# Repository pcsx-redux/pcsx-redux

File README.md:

<a href='https://ko-fi.com/nicolasnoble' target='_blank'>Buy Me a Coffee at ko-fi.com</a>

|Platform|Build status|Download|
|--------|------------|--------|
|Windows x64 build||[Windows Intel 64-bits](https://distrib.app/pub/org/pcsx-redux/project/dev-win-x64)|
|Linux x64 build||[Linux Intel 64-bits (AppImage)](https://distrib.app/pub/org/pcsx-redux/project/dev-linux-x64)|
|Linux arm64 build||[Linux Arm 64-bits (AppImage)](https://distrib.app/pub/org/pcsx-redux/project/dev-linux-arm64)|
|macOS build||[macOS Arm](https://distrib.app/pub/org/pcsx-redux/project/dev-macos-arm)|
|Browser build||[Run in the browser (experimental)](https://tools.psx.dev/redux/)|

To discuss this emulator specifically, please join our Discord server:

To discuss PlayStation 1 development, hacking, and reverse engineering in general, please join the PSX.Dev Discord server:

# PCSX-Redux

## What?
The PCSX-Redux project is a collection of tools, research, hardware design, and libraries aiming at development and reverse engineering on the PlayStation 1. The core product itself, PCSX-Redux, is yet another fork of the Playstation emulator, PCSX. While the work here is very much in progress, the goal is roughly the following:

 - Bring the codebase to more up to date code standards.
 - Get rid of the plugin system and create a single monolithic codebase that handles all aspects of the playstation emulation.
 - Write everything on top of OpenGL3+/ImGui for portability and readability.
 - Improve the debugging experience.
 - Improve the rendering experience.

Please consult [the documentation pages](https://pcsx-redux.consoledev.net) for more information on the emulator itself.

The [tools](tools) directory contains a few tools that can be used to work with PlayStation 1 software. The [wiki](https://github.com/pcsx-redux/pcsx-redux/wiki) directory contains a few research information that are not directly related to the emulator itself. The [mips](https://github.com/pcsx-redux/nugget) directory (the nugget submodule, checked out at `src/mips`) contains various pieces of code targeting the PlayStation 1, and importantly, the OpenBIOS project, which is a MIPS R3000A BIOS implementation that can be used to boot PlayStation 1 games without the need for a retail BIOS. And the [hardware](hardware) directory contains various hardware designs that can be used with the PlayStation 1.

## Where?
|Download page|
|--------|
|[Windows Intel 64-bits](https://distrib.app/pub/org/pcsx-redux/project/dev-win-x64)|
|[Windows Intel 64-bits CLI](https://distrib.app/pub/org/pcsx-redux/project/dev-win-cli-x64)|
|[Linux Intel 64-bits (AppImage)](https://distrib.app/pub/org/pcsx-redux/project/dev-linux-x64)|
|[Linux Arm 64-bits (AppImage)](https://distrib.app/pub/org/pcsx-redux/project/dev-linux-arm64)|
|[MacOS Arm](https://distrib.app/pub/org/pcsx-redux/project/dev-macos-arm)|
|[Browser (WebAssembly, experimental)](https://tools.psx.dev/redux/)|

All native builds are 64-bit only, and need a GPU and driver that can create at least an OpenGL 3.0 context. The emulator asks for a 3.3 core profile first and falls back to 3.0 if that fails.

The browser build is highly experimental and not really functional yet: expect missing features and breakage. It is redeployed from each push to main whose wasm build succeeds. It runs the CPU interpreter only and boots OpenBIOS, and it needs WebGL2 and SharedArrayBuffer. The first visit reloads the page once to enable SharedArrayBuffer.

The Linux AppImages are built on Ubuntu 24.04 and need a distribution at least that recent. On older ones, the Windows build runs under Wine 11: replace `pcsx-redux.exe`, the launcher that checks for the Visual C++ runtime, with `pcsx-redux.main` renamed to `pcsx-redux.exe`. The Windows build is x86-64, so on an ARM64 host Wine needs an x86-64 emulation layer such as Box64 or FEX under it.

### Note:
The macOS version of PCSX-Redux is not currently signed with a developer certificate so you may see a security warning when opening the application.

If you see a dialog with the message:

> “PCSX-Redux” can’t be opened because Apple cannot check it for malicious software.

You can allow the application to run by doing either of the following. You only need to do this once for freshly downloaded copies of PCSX-Redux.

- Right-click the app and select Open. This signals an explicit decision on your part that you really want to open it, and adds a new "Open" button to the security warning dialog.

- Alternatively, go to macOS Settings > Privacy & Security. Scroll down to see a section that will let you allow the app.

## How?
The code is meant to be built using very modern compilers. Also it's still fairly experimental, and lots of things can break. If you still want to proceed, here are instructions to build it on Linux, MacOS and Windows. The code now comes in two big parts: the emulator itself, and [OpenBIOS](https://github.com/pcsx-redux/nugget/tree/main/openbios), which can be used as an alternative to the retail, copyright protected BIOS.

### Getting sources
The only location for the source is [on GitHub](https://github.com/pcsx-redux/pcsx-redux/).
Clone recursively, as the project uses submodules:
```
git clone --recursive https://github.com/pcsx-redux/pcsx-redux.git
```

### Windows
Install [Visual Studio 2022 Community Edition](https://visualstudio.microsoft.com/thank-you-downloading-visual-studio/?sku=Community&rel=16) using the `Desktop development with C++` workload. Open the file `vsprojects\pcsx-redux.sln`, select `pcsx-redux -> pcsx-redux`, right click, `Set as Startup Project`, and hit `F7` to build. The project follows the open-and-build paradigm with no extra step, so no specific dependency ought to be needed, as [NuGet](https://www.nuget.org/) will take care of downloading them automatically for you on the first build.

Note: If you get an error saying `hresult e_fail has been returned from a call to a com component`, you might need to delete the .suo file in vsproject/vs, restart Visual Studio and retry.

If you want to compile OpenBIOS or other PS1 software, you need to install a MIPS toolchain on Windows. You can do this by copy-pasting the following into a command prompt:

```powershell
powershell -c "& { iwr -UseBasicParsing https://bit.ly/mips-ps1 | iex }"
```

Then, open a new command prompt, and type the following:

```
mips install 16.2.0
```

To manually install this script, you can download it from [here](https://bit.ly/mips-ps1), and then install it with the following command:

```powershell
powershell -ExecutionPolicy Unrestricted -File mips.ps1 self-install C:\path\to\destination
```

You can leave the installation path blank to install the script in the Application Data folder.

Once the toolchain is installed, you can compile OpenBIOS using `make -C src/mips/openbios`.

### Linux
Run `./dockermake.sh appimage`. You need [docker](https://en.wikipedia.org/wiki/Docker_(software)) for this to work. This will create an [AppImage](https://appimage.org/) file, called `PCSX-Redux-HEAD-x86_64.AppImage` or `PCSX-Redux-HEAD-aarch64.AppImage` depending on your machine, which a self-hosted binary containing all of its required dependencies. Alternatively, if you do not want to use Docker, you can also simply install the dependencies listed below and run `make`.

#### GNU/Linux Dependencies

If you're only interested in compiling psx code, you can simply clone the pcsx-redux repo, then build the mips toolchain with [this script](https://github.com/pcsx-redux/nugget/blob/main/tools/linux-mips/spawn-compiler.sh), then follow the [PsyQ instructions](https://github.com/pcsx-redux/nugget/blob/main/psyq/README.md) (`src/mips/psyq/README.md` in your checkout) to convert the PsyQ libraries. You might find them pre-compiled online.

 - Debian derivatives ( for full emulator compilation ):

```bash
sudo apt-get install -y build-essential git make pkg-config clang g++ libcapstone-dev libfreetype-dev libavcodec-dev libavformat-dev libavutil-dev libcurl4-openssl-dev libsdl3-dev libswresample-dev libuv1-dev zlib1g-dev
```

The mips toolchain isn't packaged by Debian or Ubuntu, so build it from source:

```bash
sudo apt-get install -y wget bzip2 xz-utils bison flex texinfo libgmp-dev libmpfr-dev libmpc-dev
mkdir mips-toolchain && cd mips-toolchain
wget -O spawn-compiler.sh https://raw.githubusercontent.com/pcsx-redux/nugget/main/tools/linux-mips/spawn-compiler.sh
sudo bash spawn-compiler.sh
```

 - Arch derivatives :

The `pcsx-redux-git` package can be installed from the AUR using your AUR helper of choice (e.g., paru):

```bash
paru -S pcsx-redux-git
```

Alternatively, the following steps describe how to install dependencies and compile manually:

```bash
sudo pacman -S --needed capstone clang git make pkg-config ffmpeg libuv zlib sdl3 curl xorg-server-xvfb imagemagick
```
The AUR mipsel packages do not give a working toolchain, so build it from source:

```bash
sudo pacman -S --needed base-devel wget texinfo gmp mpfr libmpc
mkdir mips-toolchain && cd mips-toolchain
wget -O spawn-compiler.sh https://raw.githubusercontent.com/pcsx-redux/nugget/main/tools/linux-mips/spawn-compiler.sh
sudo bash spawn-compiler.sh
```
You can then just enter the 'pcsx-redux' directory and compile without using docker with `make`.

Building OpenBIOS on Linux can be done with `./dockermake.sh -C src/mips/openbios`, or with `make -C src/mips/openbios` once you have a mipsel-none-elf toolchain. If you have a different mips compiler, you'll need to override some variables, such as `PREFIX` and `FORMAT`.

### MacOS
You need MacOS Catalina or later with the latest XCode to build, as well as a few [homebrew](https://brew.sh/) packages. Run the [brew installation script](https://github.com/pcsx-redux/pcsx-redux/blob/main/.github/scripts/install-brew-dependencies.sh) to get all the necessary dependencies. Simply run `make` to build.

Compiling OpenBIOS will require a mips compiler, which you can install from our [Homebrew tap](https://github.com/pcsx-redux/homebrew-mips):
```bash
brew install pcsx-redux/mips/mipsel-none-elf-gcc
```

Then, you can compile OpenBIOS using `make -C ./src/mips/openbios`.

## Who?
I used to contribute to the PCSX codebase. It is very likely that a sourceforge account of mine still has write access to the old cvs repository for PCSX. A long time ago, I contributed the telnet debugger, and the parallel port support. This means I am fairly familiar with this codebase, and I am also ashamed of the contributions I have done 15+ years ago, as one should.

Since the inception of this codebase, several people have contributed to it. Please refer to the [AUTHORS](AUTHORS) file for a (hopefully) exhaustive list.

## Why?
When Sony released the Playstation Classic recently, I came to realize two things: first, the state of the Playstation emulation isn't that great, and second, the only half-decent debugging tool still available for this console is that old telnet debugger I wrote eons ago, while other emulators out there for other consoles gained a lot of debugging superpowers. I think it was time for the Playstation emulation to get to better standards with regards to debuggability. I also felt I had a responsability to cleaning up some of the horrors I've introduced myself in the codebase long ago, and that made me cry a little looking at them. Hopefully, I got better at programming. Hopefully.

## Status?
The codebase still requires a lot of cleanup, and while the product is usable in its current state and lots can be achieved with it, there is still ways to go for reaching the first stable release. If you want to help with localization, you can find the translation project [on transifex](https://explore.transifex.com/grumpycoders/pcsx-redux/).

### What works?
- Dynamic Recompiler (x86-64, experimental arm64 support)
- interpreted CPU
- software GPU
- OpenGL GPU (highly experimental, still in active development)
- support for visual enhancements:
  - Linear and nearest neighbour filtering (Software and OpenGL renderer)
  - Rendering in true colour (Results in better colours, OpenGL renderer only)
  - Antialiasing (Implemented via MSAA, OpenGL renderer only)
  - Ability to optionally render polygons as wireframe or as vertices (Helps with debugging, OpenGL renderer only)
  - Hopefully more to come in the feature, such as upscaling, integer scaling, PGXP, and more
- VRAM viewer and debugger
- fully featured MIPS debugger
- memory cards
- memory card manager
- XBox controller support
- digital and analog controller emulation, Playstation Mouse emulation
- Lua scripting
- SPU debugger
- in-app shader editor and built-in crt-lottes shader
- customizable UI
- save states

### What still requires some work?
- fix remaining OpenGL renderer bugs (No mask bit emulation, missing commands, etc) and add more graphics enhancements
- proper SPU multithreaded code
- better customization
- more generic dynarec
- hook more emulator functions to Lua
- see [TODO](TODO.md) for more

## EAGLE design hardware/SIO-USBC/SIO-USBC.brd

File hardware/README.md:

# Hardware

This directory contains various hardware mods and addons for the PlayStation 1. The PCBs have been designed using Eagle, and pre-rendered gerber files are provided. When applicable, [jlcpcb](https://jlcpcb.com) build files are provided (BoM and assembly CSV files).

Some of these designs have been thoroughly documented [in the wiki](https://github.com/pcsx-redux/pcsx-redux/wiki).

* [MC-Breakout](MC-Breakout) - A breakout board for the PlayStation 1's memory card slot. This board is made to fit directly into the slot without a case, and provides a simple header to connect to the memory card slot's signals.

* [PIO-Breakout](PIO-Breakout) - A breakout board for the PlayStation 1's parallel I/O port. This board is designed to function as a pass-through, which can then be used to sniff the parallel I/O port's signals when connecting another flash cart to it.

* [PIO-Dev](PIO-Dev) - A development board for the PlayStation 1's parallel I/O port. The board has [extensive documentation](https://github.com/pcsx-redux/pcsx-redux/wiki/PIODev-Board) on the wiki.

* [PIO-Dev-Lite](PIO-Dev-Lite) - A smaller version of the PIO-Dev board, with a few less features. It is fitted with a writable flash, an FT232H chip for fast communication, and header pins to connect a [CH376 module](https://www.google.com/search?q=ch376+module). The CH376 module can be used with [Skitchin's project](https://github.com/johnbaumann/psx-wch376s) to access USB mass storage.

* [Pico-Dev](Pico-Dev) - A development board for the PlayStation 1 based on the Raspberry Pi Pico. It is extremely simple to manufacture, as its BoM is exactly one [RP2040-Zero](https://www.waveshare.com/rp2040-zero.htm), one PIO port, and one Schottky diode. The firmware for it is avaiable at [https://github.com/johnbaumann/PicoDev](https://github.com/johnbaumann/PicoDev).

* [PowerReplayUSB](PowerReplayUSB) - An easy to build mod for the popular and readily available [Power Replay Flash Cart](https://www.aliexpress.com/w/wholesale-ps1-power-replay.html) which adds USB support to it. The USB support is provided by the [FT232H](https://ftdichip.com/products/ft232hq/) chip, and [unirom](https://unirom.github.io/) has support for it. There is a [USB-C alternative](PowerReplayUSBC) available as well.

* [SIO-USBC](SIO-USBC) - A connector for the serial port of the PS1, which can directly plug into the back of the console and provide a USB-C connection uplink to the computer. Supports high-speed data transfer over USB-C using the CP2102 or CP2102N chips. The "narrow" variant is designed to fit inside a 3D printed case. If possible, use the CP2102N chip for faster communication speeds. This needs to be manufactured on a PCB that is no thicker than 1.2mm or it won't fit. PCBs thinner than 1.2mm haven't been tested yet.

The projects featuring FT232H chips can be used for ultra fast communication between the PlayStation 1 and a computer. [Tools made by danhans42](https://github.com/danhans42/psx232h) can be used for this.

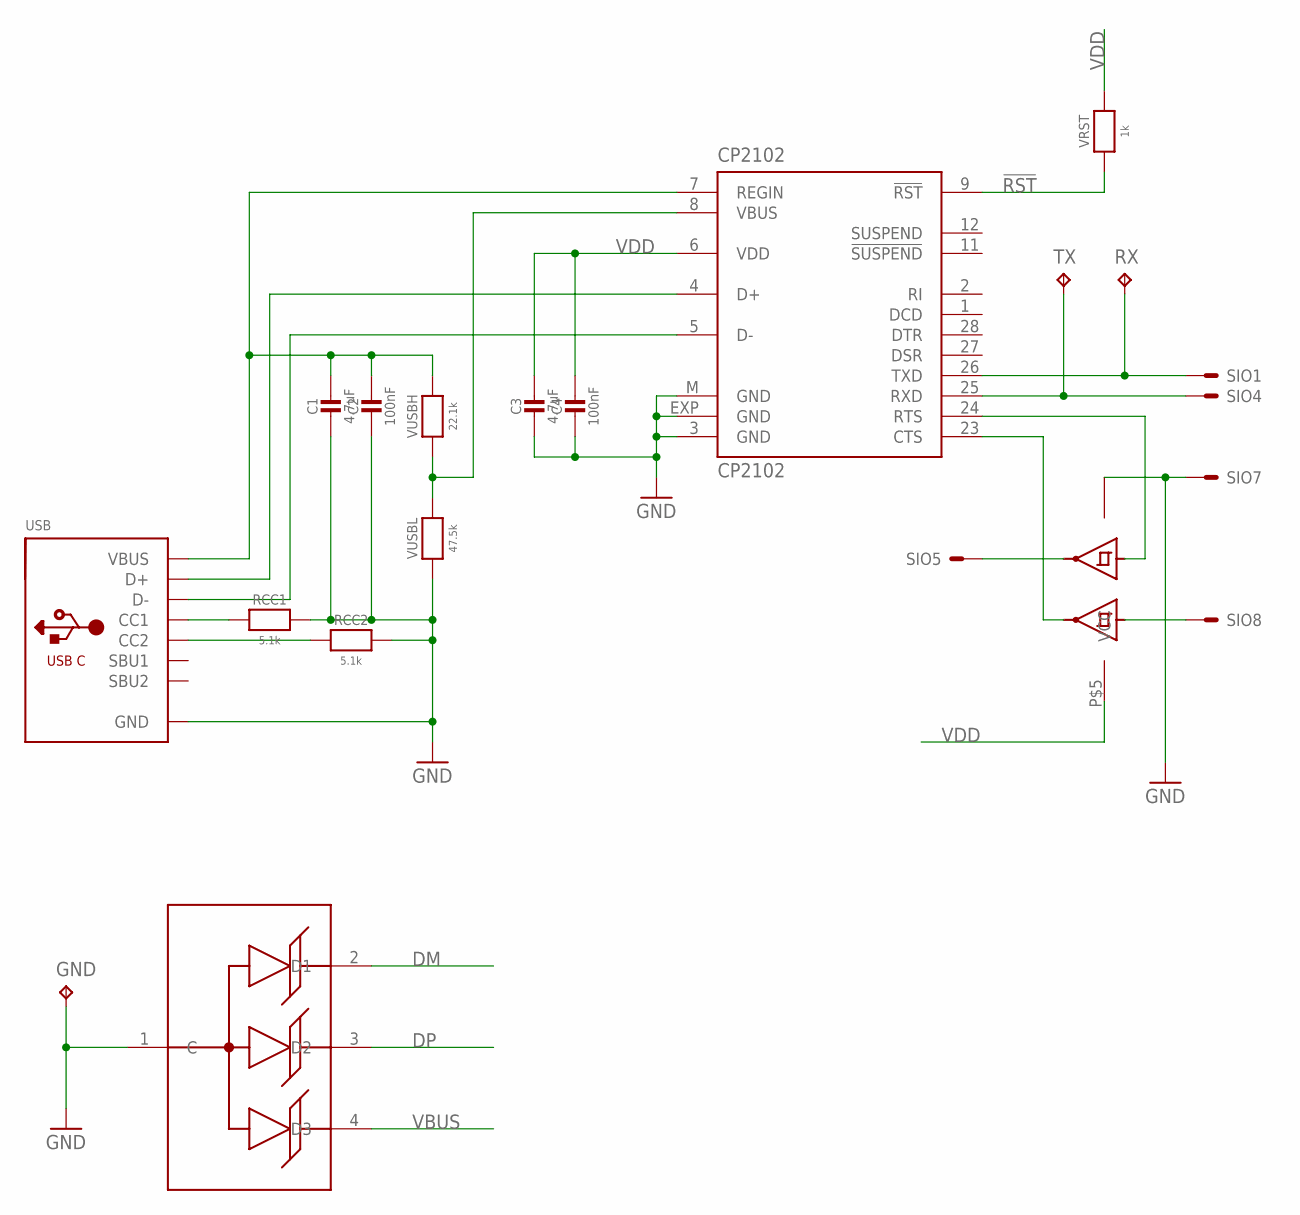
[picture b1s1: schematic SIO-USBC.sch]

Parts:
C1, C3: 4.7uF; 0603
C2, C4: 100nF; 0603
CP2102: CP2102; MLP28
GATES: 74AUP2G14; X2-DFN1410-6
GND: TPB2,54; B2,54
RCC1, RCC2: 5.1k; 0402
RX: TPB2,54; B2,54
SIO1, SIO4, SIO5, SIO7, SIO8: 1565322-1
TVS: SP0503BAHTG; SOT143
TX: TPB2,54; B2,54
USB: USB-C
VRST: 1k; 0402
VUSBH: 22.1k; 0402
VUSBL: 47.5k; 0402

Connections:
!CTS: GATES.P$1 (1A), SIO8.PAD, SIO8.PAD1
!RST: CP2102.9 (!RST), VRST.1
!RTS: GATES.P$4 (2Y), SIO5.PAD, SIO5.PAD1
CC1: RCC1.1, USB.A5 (CC1)
CC2: RCC2.1, USB.B5 (CC2)
CTS: CP2102.23 (CTS), GATES.P$6 (1Y)
DM: CP2102.5 (D-), TVS.2 (D1), USB.A7 (D-), USB.B7 (D-)
DP: CP2102.4 (D+), TVS.3 (D2), USB.A6 (D+), USB.B6 (D+)
GND: C1.2, C2.2, C3.2, C4.2, CP2102.3 (GND), CP2102.EXP (GND), CP2102.M (GND), GATES.P$2 (GND), GND.TP, RCC1.2, RCC2.2, SIO7.PAD, SIO7.PAD1, TVS.1 (C), USB.A1B12 (GND), USB.B1A12 (GND), USB.M1 (GND), USB.M2 (GND), USB.M3 (GND), USB.M4 (GND), VUSBL.1; also elsewhere on the board
RTS: CP2102.24 (RTS), GATES.P$3 (2A)
RXD: CP2102.25 (RXD), SIO4.PAD, SIO4.PAD1, TX.TP
TXD: CP2102.26 (TXD), RX.TP, SIO1.PAD, SIO1.PAD1
VBUS: C1.1, C2.1, CP2102.7 (REGIN), TVS.4 (D3), USB.A4B9 (VBUS), USB.B4A9 (VBUS), VUSBH.2
VDD: C3.1, C4.1, CP2102.6 (VDD), GATES.P$5 (VCC), VRST.2; also elsewhere on the board
VSENSE: CP2102.8 (VBUS), VUSBH.1, VUSBL.2

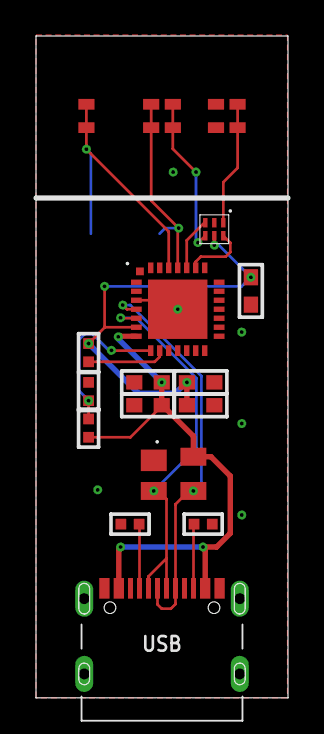
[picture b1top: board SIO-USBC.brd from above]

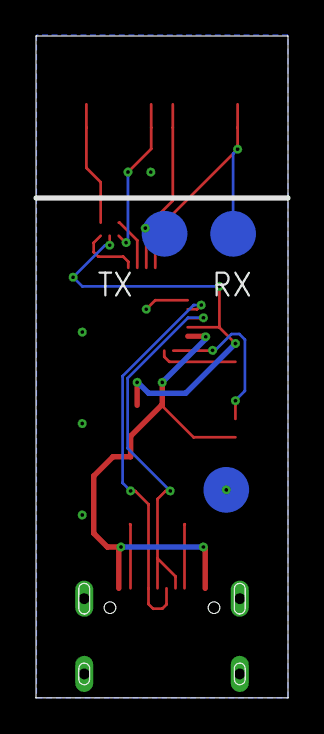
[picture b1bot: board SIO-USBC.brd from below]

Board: 2 copper layers, 14.0 x 36.8 mm, 22 parts (3 on the bottom side), 15 nets.

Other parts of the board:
C5: 100nF; 0603

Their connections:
GND: C5.1; also elsewhere on the board
VDD: C5.2; also elsewhere on the board

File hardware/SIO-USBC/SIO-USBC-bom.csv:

Comment,Designator,Footprint,LCSC Part #
4.7uF,"C1,C3",0603,C19666
100nF,"C2,C4,C5",0603,C14663
CP2102N,CP2102N,MLP28,C964632
5.1k,"RCC1,RCC2",0402,C25905
1565322-1,"SIO1,SIO4,SIO5,SIO7,SIO8",TE_1565322-1,C3308749
SP0503BAHTG,TVS,SOT143,C7074
TYPE-C-31-M-12,USB,USB-C,C165948
74AUP2G14,GATES,X2-DFN1410-6,C842416
1k,VRST,0402,C11702
22.1k,VUSBH,0402,C163478
47.5k,VUSBL,0402,C2930010
